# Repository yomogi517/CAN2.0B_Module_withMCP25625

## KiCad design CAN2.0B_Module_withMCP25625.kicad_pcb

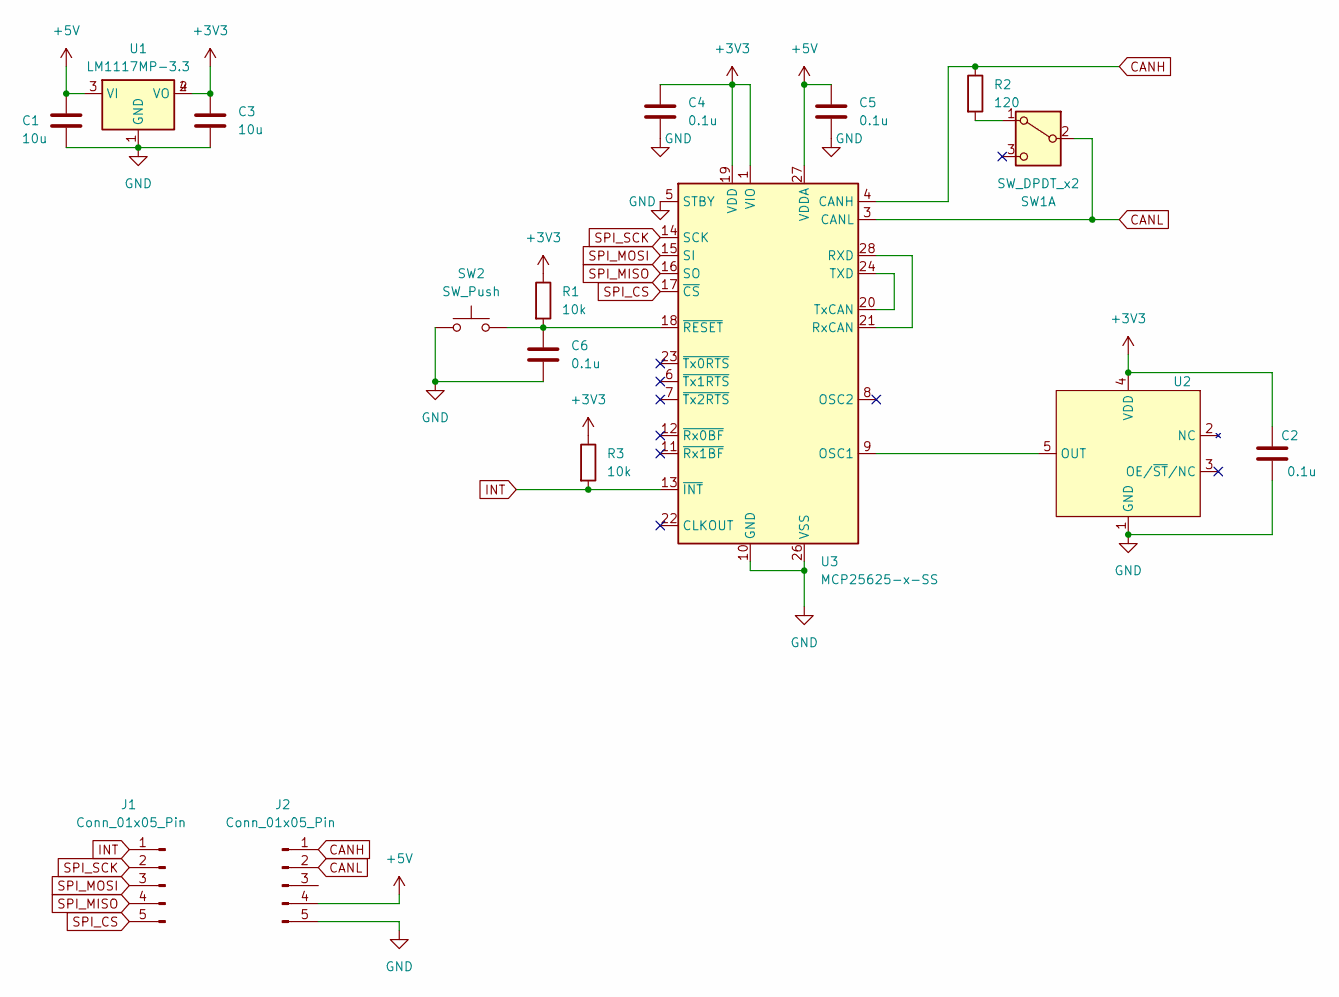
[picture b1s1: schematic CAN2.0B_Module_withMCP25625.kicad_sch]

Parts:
C1, C3: 10u; C_0603_1608Metric
C2, C4, C5, C6: 0.1u; C_0603_1608Metric
J1, J2: Conn_01x05_Pin; PinHeader_1x05_P2.54mm_Vertical
R1, R3: 10k; R_0603_1608Metric
R2: 120; R_0603_1608Metric
SW1: SW_DPDT_x2; SSSS213202
SW2: SW_Push; SW_PUSH_6mm_H7.3mm
U1: LM1117MP-3.3; SOT-223
U2: SOT-23-5_HandSoldering
U3: MCP25625-x-SS; SSOP-28_5.3x10.2mm_P0.65mm

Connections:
+3V3: C2.1, C3.1, C4.1, R1.1, R3.1, U1.2 (VO), U1.4 (VO), U2.4 (VDD), U3.1 (VIO), U3.19 (VDD)
+5V: C1.1, C5.1, J2.4, U1.3 (VI), U3.27 (VDDA)
CANH: J2.1, R2.1, U3.4 (CANH)
CANL: J2.2, SW1.2 (B), U3.3 (CANL)
GND: C1.2, C2.2, C3.2, C4.2, C5.2, C6.2, J2.5, SW2.1, U1.1 (GND), U2.1 (GND), U3.5 (STBY), U3.10 (GND), U3.26 (VSS)
INT: J1.1, R3.2, U3.13 (~INT)
unnamed: R2.2, SW1.1 (A)
unnamed: U2.5 (OUT), U3.9 (OSC1)
unnamed: U3.21 (RxCAN), U3.28 (RXD)
unnamed: U3.20 (TxCAN), U3.24 (TXD)
unnamed: C6.1, R1.2, SW2.2, U3.18 (~RESET)
SPI_CS: J1.5, U3.17 (~CS)
SPI_MISO: J1.4, U3.16 (SO)
SPI_MOSI: J1.3, U3.15 (SI)
SPI_SCK: J1.2, U3.14 (SCK)

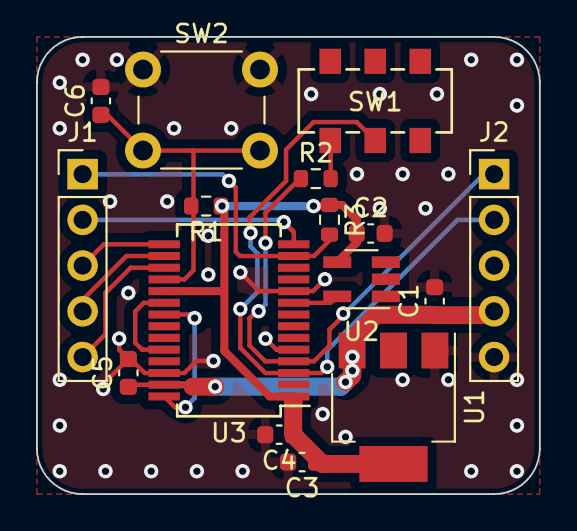
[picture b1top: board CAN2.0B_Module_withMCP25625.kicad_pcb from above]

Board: 2 copper layers, 27.9 x 25.4 mm, 16 parts (0 on the bottom side), 15 nets.

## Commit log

2024-05-16 add via
